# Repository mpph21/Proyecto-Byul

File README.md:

# Proyecto-Byul
Robot capaz de difundir información sobre primeros auxilios, además de medir diferentes parámetros vitales.

*INTRODUCCIÓN*

El presente proyecto muestra el proceso de diseño de un robot capaz de difundir información sobre el proceso de brindar primeros auxilios, además de medir diferentes parámetros vitales y con estos brindar recomendaciones de cómo actuar de acuerdo al estado en el que se encuentra la persona analizada. Este se basa en la problemática existente del desconocimiento en primeros auxilios y los efectos que tiene este desconocimiento en la población. Para el desarrollo del proyecto se optó por escoger la población de la Universidad Nacional de Colombia (Sede Bogotá), puesto se determinó que sería un entorno óptimo para la implementación del artefacto.

*PRODUCTO MÍNIMO VIABLE*

El producto mínimo viable a construir para el proyecto es un robot con un diseño muy básico, capaz de dar información acerca de los primeros auxilios que no necesiten de una capacitación especializada, además, siendo capaz de medir los parámetros de vitalidad básicos. Con el fin de educar a los estudiantes de la comunidad universitaria acerca de la aplicación de primeros auxilios.

[Byul Encuentro Ingenia Futuro 2024-1S.pdf](https://github.com/user-attachments/files/17123102/Byul.Encuentro.Ingenia.Futuro.2024-1S.pdf)

VIDEO SUSTENTACIÓN https://drive.google.com/file/d/1y00nmVABIv68McBKW9m6ADhYE01oZToh/view?usp=sharing

VIDEO FUNCIONAMIENTO: https://youtu.be/uoFE4L-aYWc

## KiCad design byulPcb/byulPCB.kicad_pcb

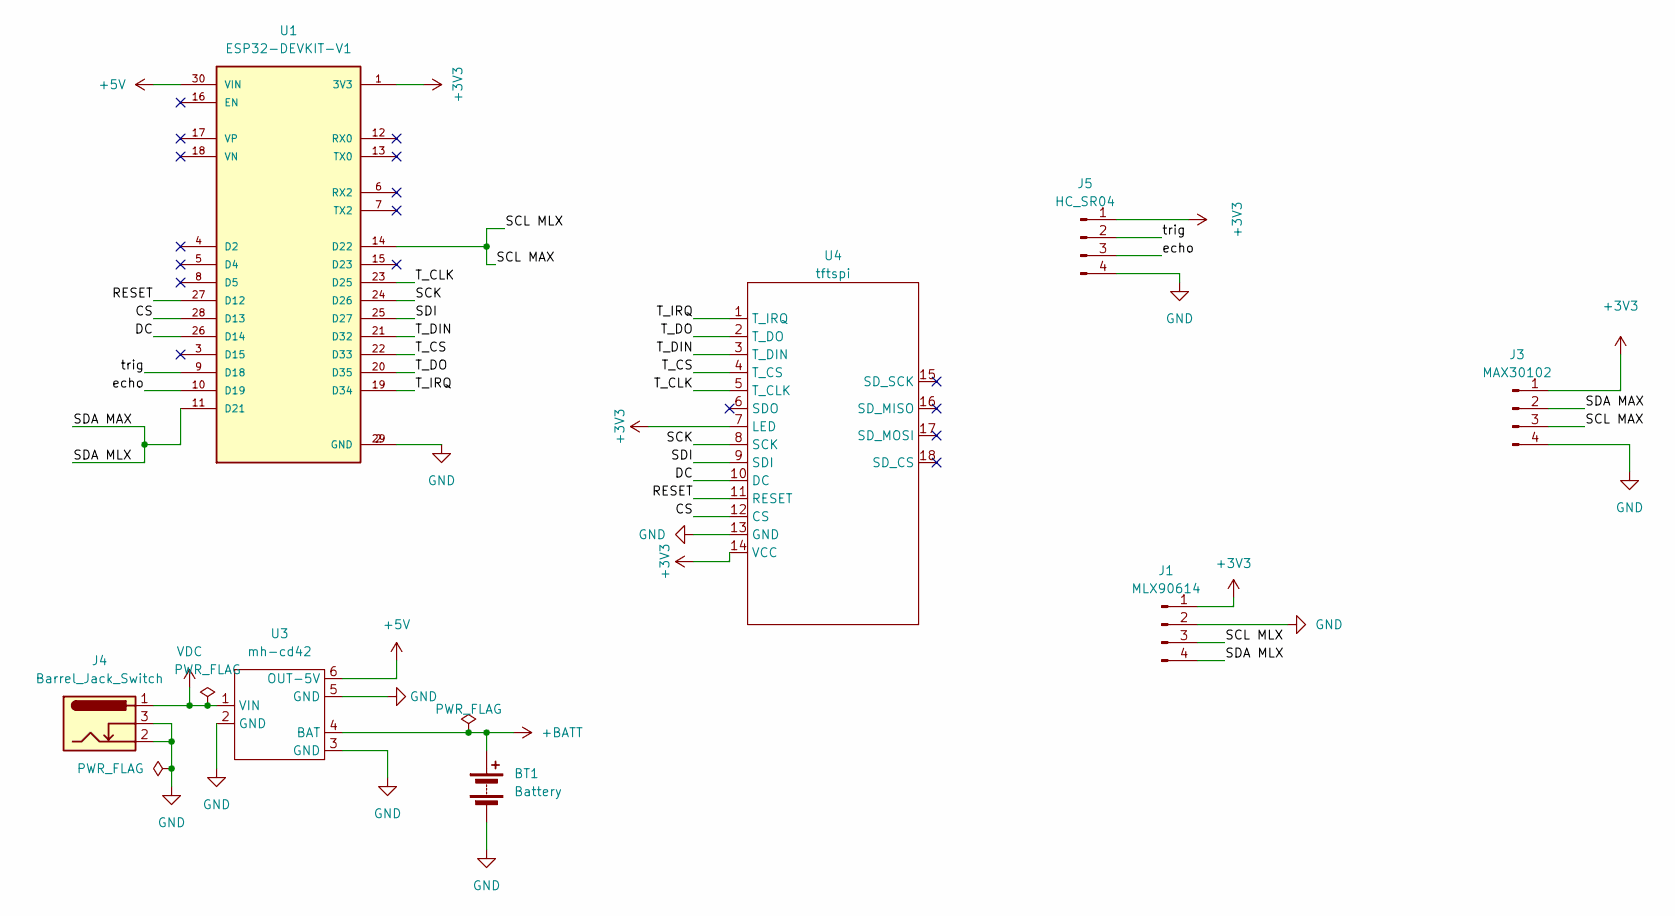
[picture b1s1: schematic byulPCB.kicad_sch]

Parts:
BT1: Battery; BatteryHolder_MPD_BH-18650-PC2
J1: MLX90614; PinHeader_1x04_P2.54mm_Vertical
J3: MAX30102; PinHeader_1x04_P2.54mm_Vertical
J4: Barrel_Jack_Switch; BarrelJack_Horizontal
J5: HC_SR04; PinHeader_1x04_P2.54mm_Vertical
U1: ESP32-DEVKIT-V1; MODULE_ESP32_DEVKIT_V1; PARTREV N/A
U3: mh-cd42
U4: tftspi

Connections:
+3V3: J1.1, J3.1, J5.1, U1.1 (3V3), U4.7 (LED), U4.14 (VCC)
+5V: U1.30 (VIN), U3.6 (OUT-5V)
+BATT: BT1.1 (+), U3.4 (BAT)
/CS: U1.28 (D13), U4.12 (CS)
/DC: U1.26 (D14), U4.10 (DC)
/RESET: U1.27 (D12), U4.11 (RESET)
/SCK: U1.24 (D26), U4.8 (SCK)
/SCL MAX: J1.3, J3.3, U1.14 (D22)
/SDA MAX: J1.4, J3.2, U1.11 (D21)
/SDI: U1.25 (D27), U4.9 (SDI)
/T_CLK: U1.23 (D25), U4.5 (T_CLK)
/T_CS: U1.22 (D33), U4.4 (T_CS)
/T_DIN: U1.21 (D32), U4.3 (T_DIN)
/T_DO: U1.20 (D35), U4.2 (T_DO)
/T_IRQ: U1.19 (D34), U4.1 (T_IRQ)
/echo: J5.3, U1.10 (D19)
/trig: J5.2, U1.9 (D18)
GND: BT1.2 (-), J1.2, J3.4, J4.2, J4.3, J5.4, U1.2 (GND), U1.29 (GND), U3.2 (GND), U3.3 (GND), U3.5 (GND), U4.13 (GND)
VDC: J4.1, U3.1 (VIN)

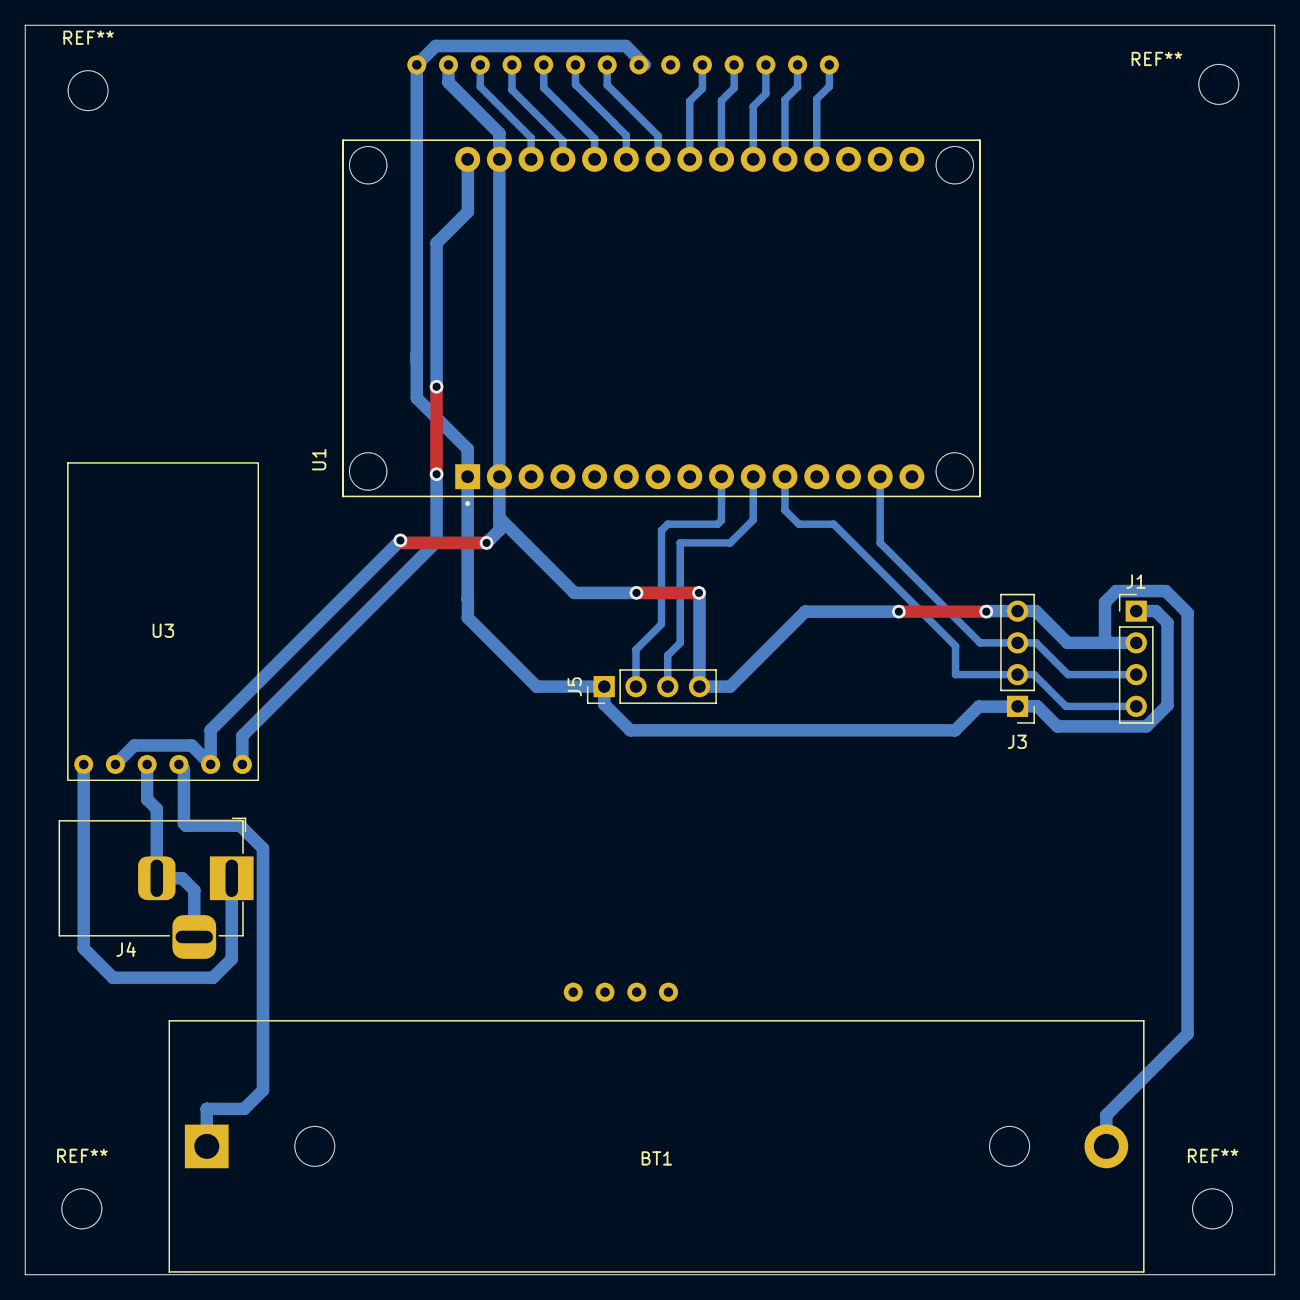
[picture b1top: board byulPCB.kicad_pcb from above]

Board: 2 copper layers, 100.0 x 100.0 mm, 8 parts (1 on the bottom side), 19 nets.

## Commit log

2024-09-26 documentación kicad
2024-09-26 Add files via upload
    Poster del proyecto
2024-09-26 Add files via upload
    Poster proyecto unal
2024-09-26 Add files via upload
    Resultado_final
2024-09-26 Add files via upload
    Cronograma
2024-09-26 Add files via upload
    Diagrama_de_caja_negra
2024-09-26 Add files via upload
    Diseño robot e implementación
2024-09-26 Add files via upload
    PCB interconectada
2024-09-26 Add files via upload
    Quema de la esp32
2024-09-26 Add files via upload
    Ensamblaje de los distintos componentes del prototipo para su presentación final.
2024-09-26 Add files via upload
    Compra de componentes
2024-09-26 Add files via upload
    diagrama
2024-09-26 Add files via upload
    Interfaces
